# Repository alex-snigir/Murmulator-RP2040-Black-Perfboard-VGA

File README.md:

*Read this document in English: [README_EN.md](README_EN.md)*

# Мурмулятор — RP2040 Black Clone, VGA-сборка на перфборде

Сборка Мурмулятора (переходной платы от Raspberry Pi Pico / клона YD-RP2040 к периферии) с VGA-выходом, PS/2-клавиатурой, двумя джойстик-портами (с поддержкой Bluetooth-геймпадов через BlueRetro), аудиовыходом, аудиовходом для загрузки программ, слотом MicroSD и внешним питанием. Плата собирается на перфборде, схема разведена в KiCad.

## Разъёмы платы

| Разъём | Назначение |
|---|---|
| J1 | Внешнее питание (PSU), DC Jack → шина `+5V_RAW` |
| J2 | Отвод шины `+5V_RAW` — для внешней периферии (BlueRetro) |
| J3 | VGA (12-контактная гребёнка, Conn_02x06) |
| J4 | Клавиатура (PS/2, Mini-DIN-6) |
| J5 | Внешний разъём (EXT, 40 пинов); пары пинов с джамперами подключают PS/2, звук и аудиовход к GPIO |
| J6 | Джойстик 1 (DE-9) |
| J7 | Джойстик 2 (DE-9) |
| J8 | Аудиовыход |
| J9 | Аудиовход (загрузка программ с TAP/магнитофона) |
| J10 | Отвод `+3V3` (JST-XH) |
| J11 | Отвод узла `+5V_VOUT` (тот же узел, что и клавиатура J4) |
| J12 | Второй вход питания от USB (модуль Micro USB) вместо DC-джека → через D1 на шину `+5V_RAW` |
| J13 | Селектор (перемычка): `+5V_RAW` → Vin (штатно) или → Vout |
| J14 | Перемычка в обход D1 |
| J15 | Модуль MicroSD (SPI) |
| J16 | Дубль J2 на другой стороне платы |

## Документация

- [`doc/murmulator-vga-project-summary.md`](doc/murmulator-vga-project-summary.md) — полное описание сборки (RU): доработка SD-модуля, VGA, PS/2-клавиатура, джойстики и интеграция BlueRetro, аудиовыход и аудиовход, разъём J5, питание, чек-лист сборки. Английская версия: [`doc/murmulator-vga-project-summary_EN.md`](doc/murmulator-vga-project-summary_EN.md).
- [`doc/rp2040-module-powerchain-analysis.md`](doc/rp2040-module-powerchain-analysis.md) — сравнение цепей питания YD-RP2040 (Black Clone) и официального Raspberry Pi Pico. Английская версия: [`doc/rp2040-module-powerchain-analysis_EN.md`](doc/rp2040-module-powerchain-analysis_EN.md).
- [`doc/Firmware/technocat-murmulator-keyboard-mapping.md`](doc/Firmware/technocat-murmulator-keyboard-mapping.md) — маппинг PS/2-клавиатуры на ZX Spectrum в прошивке Tecnocat v0.96.20, разбор режима «Cursor joystick». Английская версия: [`doc/Firmware/technocat-murmulator-keyboard-mapping_EN.md`](doc/Firmware/technocat-murmulator-keyboard-mapping_EN.md).
- [`doc/murmulator-ps2-modifiers-oscillograms.pdf`](doc/murmulator-ps2-modifiers-oscillograms.pdf) — осциллограммы PS/2-сигналов CLK/DATA для клавиш-модификаторов ([DOCX](doc/murmulator-ps2-modifiers-oscillograms.docx)). Английская версия: [PDF](doc/murmulator-ps2-modifiers-oscillograms_EN.pdf), [DOCX](doc/murmulator-ps2-modifiers-oscillograms_EN.docx).
- [`doc/murmulator_perfboard_front.jpg`](doc/murmulator_perfboard_front.jpg) — фото платы на перфборде (front).
- [`doc/murmulator_perfboard_back.jpg`](doc/murmulator_perfboard_back.jpg) — фото платы на перфборде (back).

## Схемы (KiCad)

- [`schematics/rp2040_black_vga/`](schematics/rp2040_black_vga/) — исходные файлы проекта KiCad.
- [`schematics/rp2040_black_vga/plot/rp2040_black_vga.pdf`](schematics/rp2040_black_vga/plot/rp2040_black_vga.pdf) — принципиальная схема в PDF.
- [`schematics/rp2040_black_vga/plot/rp2040_black_vga.net`](schematics/rp2040_black_vga/plot/rp2040_black_vga.net) — нетлист.

## Справочные материалы

- [`doc/YD-2040-2022-V1.1-Schematics_black_clone.pdf`](doc/YD-2040-2022-V1.1-Schematics_black_clone.pdf) — схема модуля YD-RP2040 (Black Clone).
- [`doc/YD-2040-2022-V1.1 - Powerchain.jpg`](<doc/YD-2040-2022-V1.1 - Powerchain.jpg>), [`doc/RP2040 Official Pico Module - Powerchain.jpg`](<doc/RP2040 Official Pico Module - Powerchain.jpg>) — фрагменты схем питания клона и официального Pico.
- [`doc/original_classic_murmulator_37NJU22_emul_RPPICO_card.pdf`](doc/original_classic_murmulator_37NJU22_emul_RPPICO_card.pdf) — оригинальная классическая схема Мурмулятора.
- [`doc/FT SD Module modification.jpg`](<doc/FT SD Module modification.jpg>) — доработка SD-модуля.

## Ключевые особенности сборки

- **SD-модуль** доработан: выпаяны AMS1117 и буфер 74VHCT125A, установлены перемычки — модуль работает как чистый 3.3V breakout без потери фронтов на высокой скорости SPI.
- **VGA** — пассивная резисторная R2R-лесенка на GPIO, без отдельного питания.
- **PS/2-клавиатура** — питание от Vout (после диода BAT54C), сигнальные линии CLK/DATA согласованы по уровню резистивно-зенерной схемой (5V → 3.3V).
- **Джойстики (Dendy, DE-9)** — сдвиговый регистр запитан от 3.3V, что снимает необходимость в защитных резисторах на DATA.
- **BlueRetro** — DIY-адаптер на ESP32 эмулирует оба джойстик-порта по Bluetooth HID (PS3/4/5, Xbox, Wii/Switch и др.), протокол CLOCK/LATCH/DATA идентичен физическому Dendy-джойстику. Требует питания на J1 или J12. Сборка адаптера на 3.3V-логике: https://github.com/alex-snigir/BlueRetro-3.3V-logic
- **Аудиовыход** — стереоканал (L/R) плюс подмешивание сигнала пищалки (BEEP_OUT).
- **Аудиовход** — двухкаскадный формирователь на транзисторах для загрузки программ с TAP-сигнала (магнитофон, телефон, онлайн-плеер TAP).
- **Питание** — шина `+5V_RAW` от DC-джека J1 или от Micro USB J12 (через диод Шоттки D1), селектор J13 подаёт её на Vin модуля (штатно, через встроенный BAT54C) или напрямую на Vout в обход маломощного BAT54C.

Подробности по каждому пункту — в [`doc/murmulator-vga-project-summary.md`](doc/murmulator-vga-project-summary.md).

## Корпус

### 3D-модели для печати

Файлы лежат в папке [`3d models/`](<3d models/>):

| Деталь | Файлы |
|---|---|
| Корпус (дно + крышка) | [`Box_Bottom_v2.STL`](<3d models/Box_Bottom_v2.STL>) + [`Box_Cover_v2.STL`](<3d models/Box_Cover_v2.STL>) |
| Только плоское дно, без крышки | [`Box_Bottom.STL`](<3d models/Box_Bottom.STL>) |
| Крепление для двух разъёмов DB9 (джойстики J6/J7) | [`DB9_x2_mount.STL`](<3d models/DB9_x2_mount.STL>) |
| Опора для SD-модуля | [`SD_module_support.STL`](<3d models/SD_module_support.STL>) |

Рядом лежат исходники SolidWorks (`.SLDPRT`) и проекты слайсера (`.3mf`) с теми же именами.

## Ссылки

- Официальная документация и другие варианты сборки Мурмулятора: https://murmulator.ru/howto
- Классическая схема (референс): https://github.com/AlexEkb4ever/MURMULATOR_classical_scheme
- Базовая версия «Мурмулятор на макетной плате 7×9 с VGA»: https://murmulator.ru/mm-maket
- BlueRetro-адаптер на 3.3V-логике (интеграция джойстик-портов): https://github.com/alex-snigir/BlueRetro-3.3V-logic
- Прошивка Tecnocat (Murmulator_rp2040): https://github.com/MadedCat/Murmulator_rp2040

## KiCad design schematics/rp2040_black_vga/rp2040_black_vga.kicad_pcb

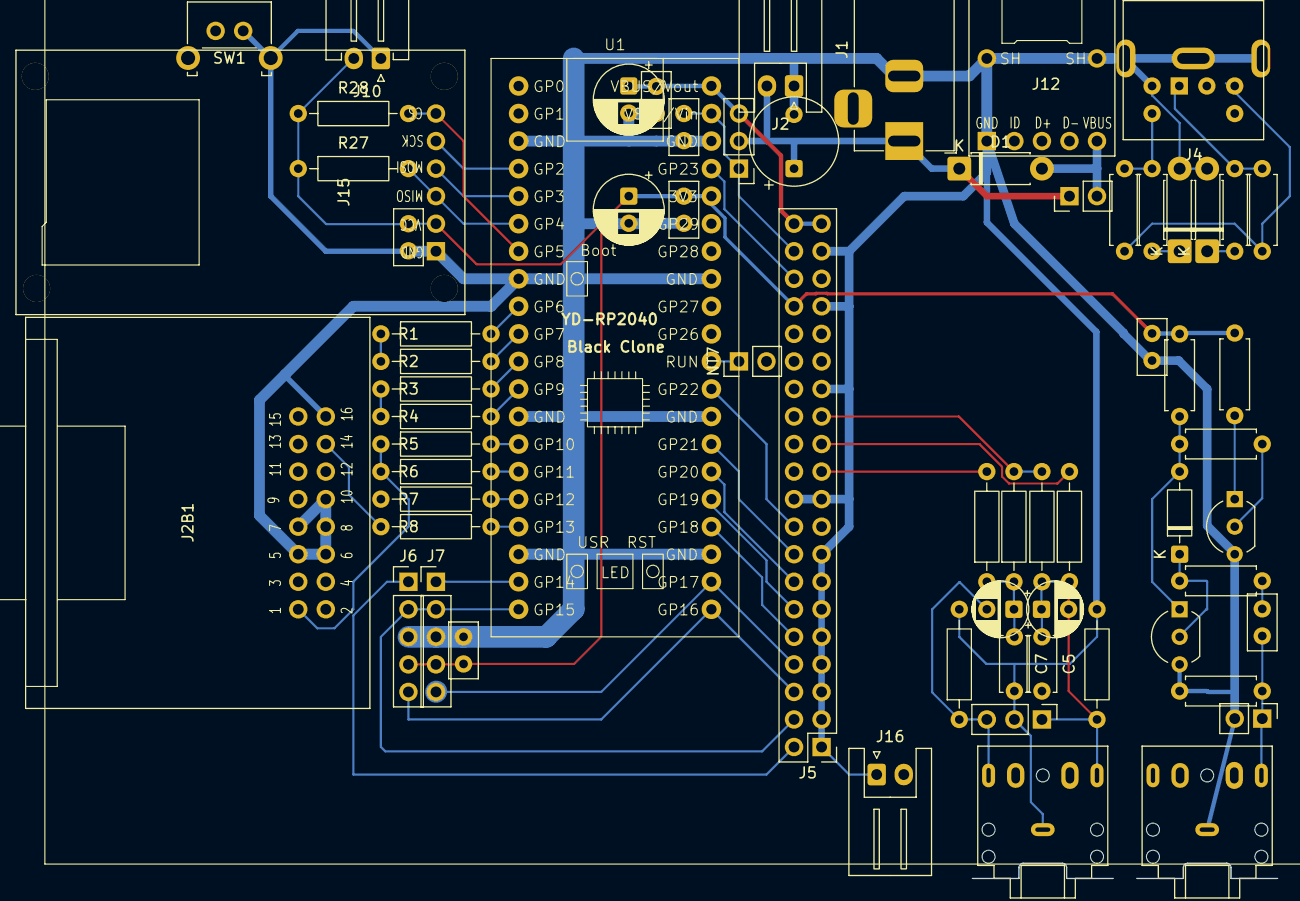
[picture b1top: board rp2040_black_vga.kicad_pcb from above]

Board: 2 copper layers, 65 parts (0 on the bottom side), 58 nets.

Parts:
C4, C6: 10uF; CP_Radial_D5.0mm_P2.50mm
C5, C7: 10nF; C_Disc_D5.0mm_W2.5mm_P5.00mm
C8, C10, C11, C12, C15, C17, C20: 100nF; C_Disc_D5.0mm_W2.5mm_P2.50mm
C16, C18: 100uF; CP_Radial_D6.3mm_P2.50mm
C19: 470uF; CP_Radial_Tantal_D8.0mm_P5.00mm
D1: 1N5819; D_DO-41_SOD81_P7.62mm_Horizontal
D2, D3: 3.3V; D_DO-41_SOD81_P7.62mm_Horizontal
D4: 4148; D_DO-35_SOD27_P7.62mm_Horizontal
J1: Jack-DC; BarrelJack_Horizontal
J2, J16: Conn_01x02; JST_XH_S2B-XH-A_1x02_P2.50mm_Horizontal
J2B1: DE15_Socket; VGA_DR15P_Module
J4: Mini-DIN-6; Connector_Mini-DIN_Female_6Pin_2rows
J5: Conn_02x20_Odd_Even; PinHeader_2x20_P2.54mm_Vertical
J6, J7: DE9_Pins; DB9_PinHeader_1x05_P2.54mm_Pins_4,3,8,6,2
J8: Audio OUT; Jack_3.5mm_CUI_SJ1-3525N_Horizontal
J8B1: OUT_A; PinHeader_1x03_P2.54mm_Vertical
J9: Audio IN; Jack_3.5mm_CUI_SJ1-3525N_Horizontal
J9B1: IN_A; PinHeader_1x02_P2.54mm_Vertical
J10: Conn_01x02; JST_XH_S2B_1x02_P2.50mm_Horizontal
J12: USB_Micro_Module_15x13.5mm
J13: Conn_01x03; PinHeader_1x03_P2.54mm_Vertical
J14: Conn_01x02; PinHeader_1x02_P2.54mm_Vertical
J15: MicroSD_Module_41.5x24.5mm
NT7: NetTie_2; PinHeader_1x02_P2.54mm_Vertical
Q1, Q2: S9014; TO-92_Inline_Wide_S9014
R1, R3, R5, R21, R25: 1K; R_Axial_DIN0207_L6.3mm_D2.2mm_P10.16mm_Horizontal
R2, R4, R6, R22, R26: 330R; R_Axial_DIN0207_L6.3mm_D2.2mm_P10.16mm_Horizontal
R7, R8: 100R; R_Axial_DIN0207_L6.3mm_D2.2mm_P10.16mm_Horizontal
R9, R10, R31: 1K; R_Axial_DIN0207_L6.3mm_D2.5mm_P7.62mm_Horizontal
R11, R12, R33: 100R; R_Axial_DIN0207_L6.3mm_D2.5mm_P7.62mm_Horizontal
R23, R24: 2K; R_Axial_DIN0207_L6.3mm_D2.2mm_P10.16mm_Horizontal
R27, R28: 10K; R_Axial_DIN0207_L6.3mm_D2.2mm_P10.16mm_Horizontal
R29, R30, R32: 10K; R_Axial_DIN0207_L6.3mm_D2.5mm_P7.62mm_Horizontal
SW1: RESET; SW_Tactile_SKHH_Angled
U1: YD-RP2040 TypeC Black Clone; RP2040_Type-C_4MB_black_with_ARGB_LED

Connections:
+3V3: C8.2, C10.2, C12.1, C15.1, C16.1, J5.34, J6.6, J7.6, J10.2, J15.2 (VCC), R27.1, R28.1, R30.1, R31.1, U1.36 (3V3)
+5V_RAW: C19.1, D1.1 (K), J1.1, J2.2, J13.2, J14.1, J16.2
/+5V_IN: C20.1, J5.38, J13.1, U1.39 (Vin)
/+5V_VOUT: C17.1, C18.1, J4.4, J5.39, J5.40, J13.3, R9.1, R10.1, U1.40 (Vout)
/BEEP_OUT: J5.25, R23.2, R24.2
/CLOCK: J5.2, J6.4, J7.4, U1.19 (GP14)
/DATA1: J5.6, J6.2, U1.21 (GP16)
/DATA2: J5.8, J7.2, U1.22 (GP17)
/GP_0: J5.32, U1.1 (GP0)
/GP_1: J5.30, U1.2 (GP1)
/GP_2: J15.5 (SCK), U1.4 (GP2)
/GP_3: J15.4 (MOSI), U1.5 (GP3)
/GP_4: J15.3 (MISO), R27.2, U1.6 (GP4)
/GP_5: J15.6 (CS), R28.2, U1.7 (GP5)
/GP_6: R1.2, U1.9 (GP6)
/GP_7: R2.2, U1.10 (GP7)
/GP_8: R3.2, U1.11 (GP8)
/GP_9: R4.2, U1.12 (GP9)
/GP_10: R5.2, U1.14 (GP10)
/GP_11: R6.2, U1.15 (GP11)
/GP_12: R7.2, U1.16 (GP12)
/GP_13: R8.2, U1.17 (GP13)
/GP_18: J5.10, U1.24 (GP18)
/GP_19: J5.12, U1.25 (GP19)
/GP_20: J5.14, U1.26 (GP20)
/GP_21: J5.16, U1.27 (GP21)
/GP_22: J5.18, U1.29 (GP22)
/GP_23: J5.36, U1.37 (GP23)
/GP_26: J5.22, U1.31 (GP26)
/GP_27: J5.24, U1.32 (GP27)
/GP_28: J5.26, U1.34 (GP28)
/GP_29: J5.28, U1.35 (GP29)
/L: C4.2, J8.T, J8B1.1, R22.1
/LATCH: J5.4, J6.3, J7.3, U1.20 (GP15)
/LEFT_OUT: J5.23, R21.2
/LOAD_IN_D: J5.17, Q2.C (E_E), R31.2
/LOAD_IN_L: C11.2, J9.T, J9B1.1, R33.1
/PS/2_CLK: J4.5, R9.2, R11.1
/PS/2_CLK_3V: D2.1 (K), J5.31, R11.2
/PS/2_DATA: J4.1, R10.2, R12.1
/PS/2_DATA_3V: D3.1 (K), J5.29, R12.2
/R: C6.2, J8.R, J8B1.3, R26.1
/RIGHT_OUT: J5.21, R25.2
/RST: J5.35, NT7.2
/RUN: NT7.1, SW1.1, U1.30 (RUN)
/VGA_B: J2B1.3, R1.1, R2.1
/VGA_G: J2B1.2, R3.1, R4.1
/VGA_HS: J2B1.13, R7.1
/VGA_R: J2B1.1, R5.1, R6.1
/VGA_VS: J2B1.14, R8.1
GND: C5.2, C7.2, C8.1, C10.1, C12.2, C15.2, C16.2, C17.2, C18.2, C19.2, C20.2, D2.2 (A), D3.2 (A), J1.2, J2.1, J2B1.5, J2B1.6, J2B1.7, J2B1.8, J2B1.10, J4.3, J5.1, J5.3, J5.5, J5.7, J5.9, J5.11, J5.13, J5.15, J5.19, J5.20, J5.27, J5.33, J5.37, J6.8, J7.8, J8.S, J8B1.2, J9.S, J9B1.2, J10.1, J12.1 (GND), J12.6 (SH), J15.1 (GND), J16.1, Q1.E, Q2.E (C_C), R22.2, R26.2, R33.2, SW1.2, U1.3 (GND), U1.8 (GND), U1.13 (GND), U1.18 (GND), U1.23 (GND), U1.28 (GND), U1.33 (GND), U1.38 (GND)
unnamed: C4.1, C5.1, R21.1, R23.1
unnamed: C6.1, C7.1, R24.1, R25.1
unnamed: C11.1, R32.1
unnamed: D1.2 (A), J12.5 (VBUS), J14.2
unnamed: D4.2 (A), Q1.C, R29.1, R30.2
unnamed: D4.1 (K), Q1.B, R32.2
unnamed: Q2.B (B_B), R29.2
